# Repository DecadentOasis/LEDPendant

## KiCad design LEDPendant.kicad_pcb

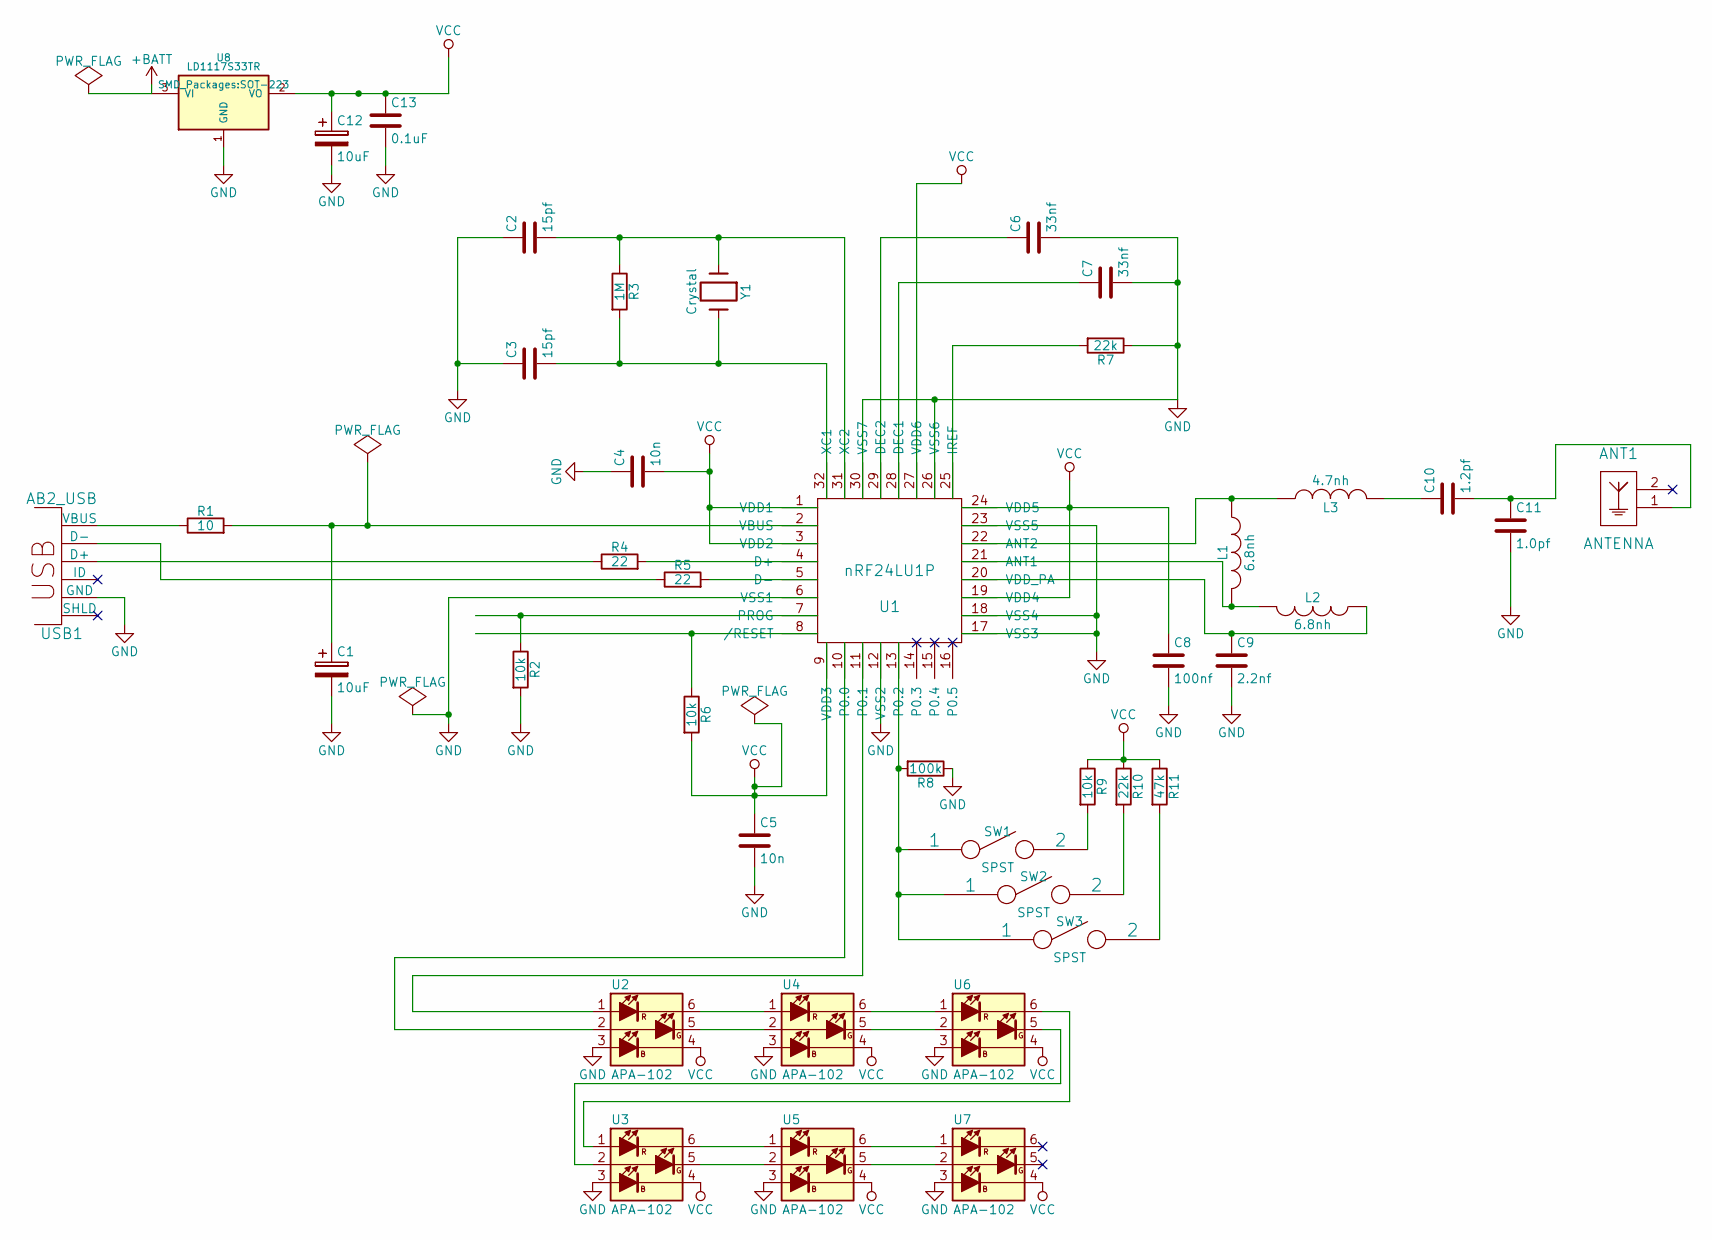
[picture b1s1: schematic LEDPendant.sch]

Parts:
ANT1: ANTENNA; Ant_Microchip_2_4G
C1, C12: 10uF; TantalC_SizeA_EIA-3216_Reflow
C2, C3: 15pf; C_0805
C4, C5: 10n; C_0805
C6, C7: 33nf; C_0805
C8: 100nf; C_0805
C9: 2.2nf; C_0805
C10: 1.2pf; C_0805
C11: 1.0pf; C_0805
C13: 0.1uF; C_0805
L1, L2: 6.8nh; R_0805
L3: 4.7nh; R_0805
R1: 10; R_0805
R2, R6, R9: 10k; R_0805
R3: 1M; R_0805
R4, R5: 22; R_0805
R7, R10: 22k; R_0805
R8: 100k; R_0805
R11: 47k; R_0805
SW1, SW2, SW3: SPST; SW_SPST_PTS645
U1: nRF24LU1P; QFN-32-1EP_5x5mm_Pitch0.5mm
U2, U3, U4, U5, U6, U7: APA-102; APA102
U8: LD1117S33TR; SOT-223
USB1: AB2_USB; AB2_USB_MICRO_SMD
Y1: Crystal; Crystal_SMD_0603_4Pads

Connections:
+BATT: U8.3 (VI); also elsewhere on the board
GND: C1.2, C2.1, C3.1, C4.1, C5.2, C6.2, C7.2, C8.2, C9.2, C11.2, C12.2, C13.2, R2.2, R7.1, R8.1, U1.6 (VSS1), U1.12 (VSS2), U1.17 (VSS3), U1.18 (VSS4), U1.23 (VSS5), U1.26 (VSS6), U1.30 (VSS7), U2.3 (GND), U3.3 (GND), U4.3 (GND), U5.3 (GND), U6.3 (GND), U7.3 (GND), U8.1 (GND), USB1.5 (GND); also elsewhere on the board
unnamed: ANT1.1, C10.2, C11.1
unnamed: C1.1, R1.2, U1.2 (VBUS)
unnamed: C2.2, R3.1, U1.31 (XC2), Y1.1
unnamed: C3.2, R3.2, U1.32 (XC1), Y1.2
unnamed: C6.1, U1.29 (DEC2)
unnamed: C7.1, U1.28 (DEC1)
unnamed: C9.1, L2.1, U1.20 (VDD_PA)
unnamed: C10.1, L3.2
unnamed: L1.1, L3.1, U1.22 (ANT2)
unnamed: L1.2, L2.2, U1.21 (ANT1)
unnamed: R1.1, USB1.1 (VBUS)
unnamed: R2.1, U1.7 (PROG)
unnamed: R4.1, USB1.3 (D+)
unnamed: R4.2, U1.4 (D+)
unnamed: R5.1, USB1.2 (D-)
unnamed: R5.2, U1.5 (D-)
unnamed: R6.1, U1.8 (/RESET)
unnamed: R7.2, U1.25 (IREF)
unnamed: R8.2, SW1.1, SW2.1, SW3.1, U1.13 (P0.2)
unnamed: R9.2, SW1.2
unnamed: R10.2, SW2.2
unnamed: R11.2, SW3.2
unnamed: U1.10 (P0.0), U2.2 (CI)
unnamed: U1.11 (P0.1), U2.1 (DI)
unnamed: U2.5 (CO), U4.2 (CI)
unnamed: U2.6 (DO), U4.1 (DI)
unnamed: U3.1 (DI), U6.6 (DO)
unnamed: U3.2 (CI), U6.5 (CO)
unnamed: U3.5 (CO), U5.2 (CI)
unnamed: U3.6 (DO), U5.1 (DI)
unnamed: U4.5 (CO), U6.2 (CI)
unnamed: U4.6 (DO), U6.1 (DI)
unnamed: U5.5 (CO), U7.2 (CI)
unnamed: U5.6 (DO), U7.1 (DI)
VCC: C4.2, C5.1, C8.1, C12.1, C13.1, R6.2, R9.1, R10.1, R11.1, U1.1 (VDD1), U1.3 (VDD2), U1.9 (VDD3), U1.19 (VDD4), U1.24 (VDD5), U1.27 (VDD6), U2.4 (VCC), U3.4 (VCC), U4.4 (VCC), U5.4 (VCC), U6.4 (VCC), U7.4 (VCC), U8.2 (VO)

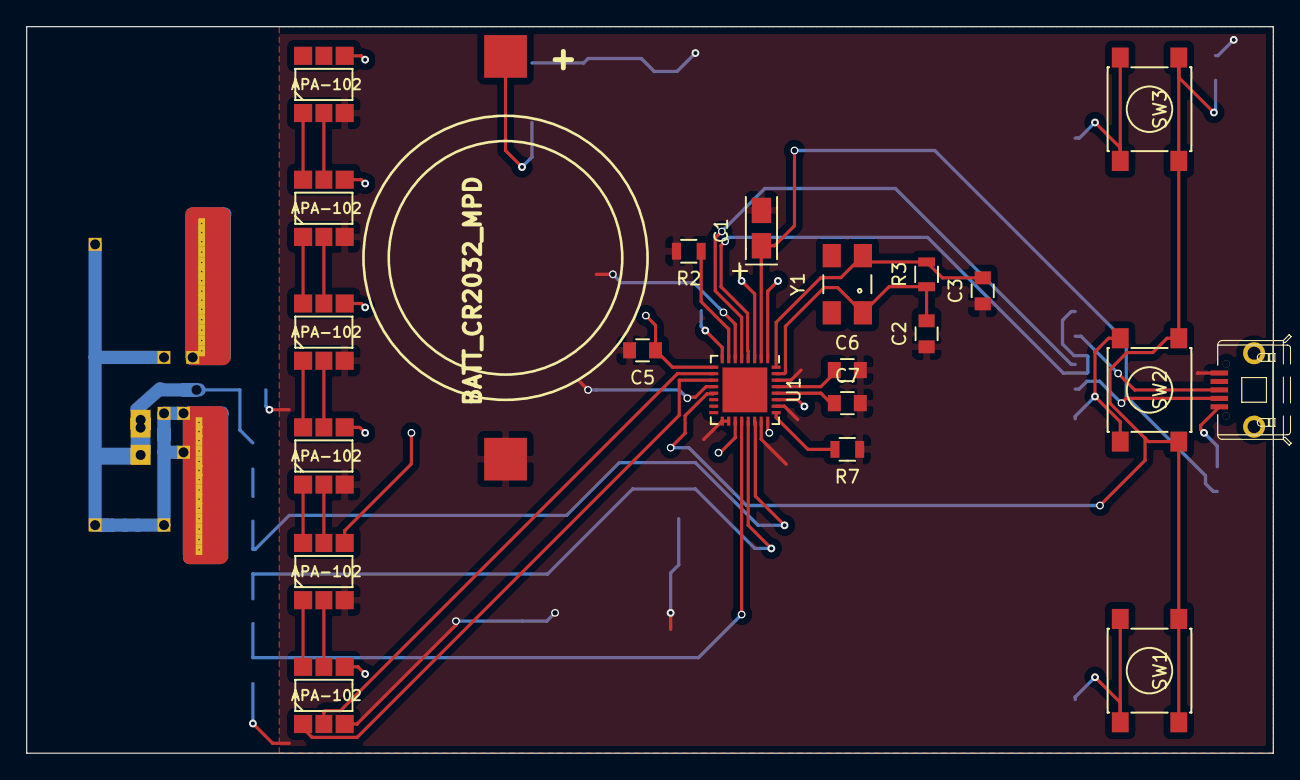
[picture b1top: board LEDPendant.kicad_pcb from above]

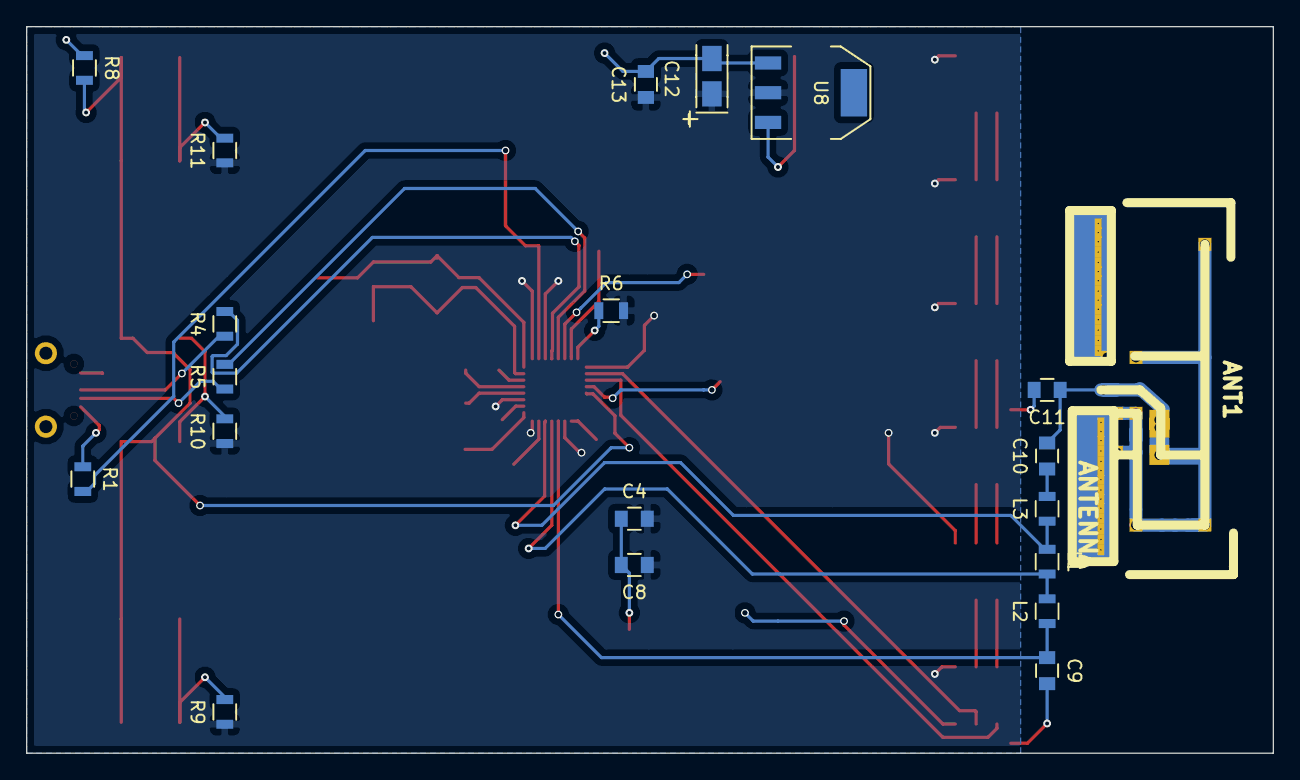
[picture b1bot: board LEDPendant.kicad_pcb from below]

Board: 2 copper layers, 95.9 x 55.9 mm, 42 parts (20 on the bottom side), 37 nets.

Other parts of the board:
BATT_CR2032_MPD: VAL**; BATT_CR2032_MPD

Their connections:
+BATT: BATT_CR2032_MPD.1; also elsewhere on the board
GND: BATT_CR2032_MPD.2; also elsewhere on the board

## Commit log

2015-05-27 Check in NRF24LU1P library
2015-05-27 Added NRF24LUP to schematic
2015-05-27 Added usb and apa102
2015-05-28 Added antenna and more wires
2015-05-30 Placed and somewhat autorouted
2015-06-01 Another pass at the large board
2015-06-01 Ignore bak files
2015-06-01 More hand routing
2015-06-02 Passing ERC/DRC
2015-06-02 Add cr2032 battery
2015-06-02 Check in latest CSV and XML
